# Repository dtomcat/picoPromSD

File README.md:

# picoPromSD
EEPROM reader/writer and OG Xbox Seagate Password retrieval for the Original Xbox that also decodes the EEPROM data

What will it do?

1. Backup the Xbox's EEPROM and save it to microSD card.
2. Can write an EEPROM backup saved to µSD card to the Xbox's EEPROM.  (has some checks to help prevent writing a bad backup to the EEPROM)
3. Decrypt the EEPROM and save the important information in plain text to the µSD card.
4. Can calculate the HDD password while backing up the EEPROM (for OEM Seagate and WD drives)
		- Requires preparing an additional file.  Video of process: [Video of Process](https://youtu.be/JSXaQWXcwFo?si=bOLGbLG80aQxxA59)
5. For OEM Seagate drives (ALL), It can grab the HDD password directly from the drive itself.  No need for EEPROM or XBOX.  [Video of Process](https://youtu.be/1lWm_fr0Neo?si=kcM-wwt6UB56qRjm)
6. For OEM Seagate drives (ALL), It can unlock the HDD directly from the drive itself.  No need for EEPROM or XBOX.  [Video of Slim](https://www.youtube.com/shorts/Nwhjg9Vyvl8), [Video of RJ](https://www.youtube.com/shorts/swidWJ0N5yo)
7. More features may be added later.
<br><br><br>
This project is based on the work from Ryzee119's ArduinoProm:

>ArduinoProm. An Arduino based Original Xbox EEPROM reader and writer.
>It can be used to recover a HDD key etc. <br><br>
>ArduinoProm is inspired and adapted upon the awesome work by Grimdoomer on PiPROM, now achievable on a <$3 Arduino board.
>See https://github.com/grimdoomer/PiPROM for the Original Raspberry Pi version!
>  
>**Use at your own risk**
>

>The firmware has been written around the Arduino Pro Micro Leonardo (5V/16Mhz). However I would expect it to work on any Arduino with a built in USB >bootloader/Virtual Comport support, and obviously I2C support.
>1. Open `ArduinoProm.ino` in [Arduino IDE](https://www.arduino.cc/en/main/software)
>2. Connect your Arduino to your PC and setup the IDE. An example below <br> 
>3. Hit the program button then confirm it compiles and programs successfully.
>
>
>By Ryzee119

This project uses code by Ryzee119, dx4m (from this [project](https://github.com/dx4m/Xbox-EEPROM-Utility)), and may contain code from various snippets from different forums (sorry lost my notes on who to thank).

This project is a continuation of my work from [ArdPromSD project](https://github.com/dtomcat/ArdPromSD).
This project was moved to an RP2040 MCU for more memory space.  This allowed me add the features I wanted to from the previous project, but ran out of program space to do so.  New features include better logging, eeprom decryption, as well as being able to retrieve the password from OEM seagate drives without the need for the original eeprom, original xbox, or even a PC!

SPECIAL THANKS!!!!<br>
Ryzee for his project above!<br>
Skye for all the HDD commands and knowledge! Invaluable addition to PPSD!<br>
Beta Testers:  Cato, Harcroft, Siktah

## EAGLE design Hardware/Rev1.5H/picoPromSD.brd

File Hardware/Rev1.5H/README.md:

## Initial release of picoPromSD
Initial release that contains everything needed to either make or have one assembled
This revision is an edit from the first release.  All edits were done by Harcroft who put a lot of time in effort into find same quality alternate parts at lower costs so picoPromSD could be build at a lower cost without sacrificing quality or functionality! <br><br>

<br>
<br>

In the main Rev1.5H directory are all the files to edit the board as you want including library of all components.

### Gerbers
- Contains all files necessary to have the PCBs made at your preferred PCB house.<br><br>

### Assembly
- Contains all files necessary to have the PCBs made and assemble at your preferred PCB house. (was made for JLCPCB, but may work with others)
    - [PicoPromSD_v1.5H_JLC_PCBA_BOM.xlsx](Assembly/PicoPromSD_v1.5H_JLC_PCBA_BOM.xlsx) and [PicoPromSD_v1.5H_top_JLC_CPL.csv](Assembly/PicoPromSD_v1.5H_top_JLC_CPL.csv) are the files JLCPCB will ask for when selecting assembly.
    - [PicoPromSD_v1.5H_LCSC_THT_BOM.xlsx](Assembly/PicoPromSD_v1.5H_LCSC_THT_BOM.xlsx) is the parts you'll need (from LCSC) that are not a part of the assembly and will need to be hand soldered on.  These are through hole components and were purposely omitted from the assembly to save costs since through hole adds a considerable amount to assembly costs.
    - [PicoPromSD_v1.5H_Digikey_BOM.xlsx] contains a full BOM to allow you to order all the parts and hand assemble the entire board. (or would just like to use parts from Digikey instead of LCSC).

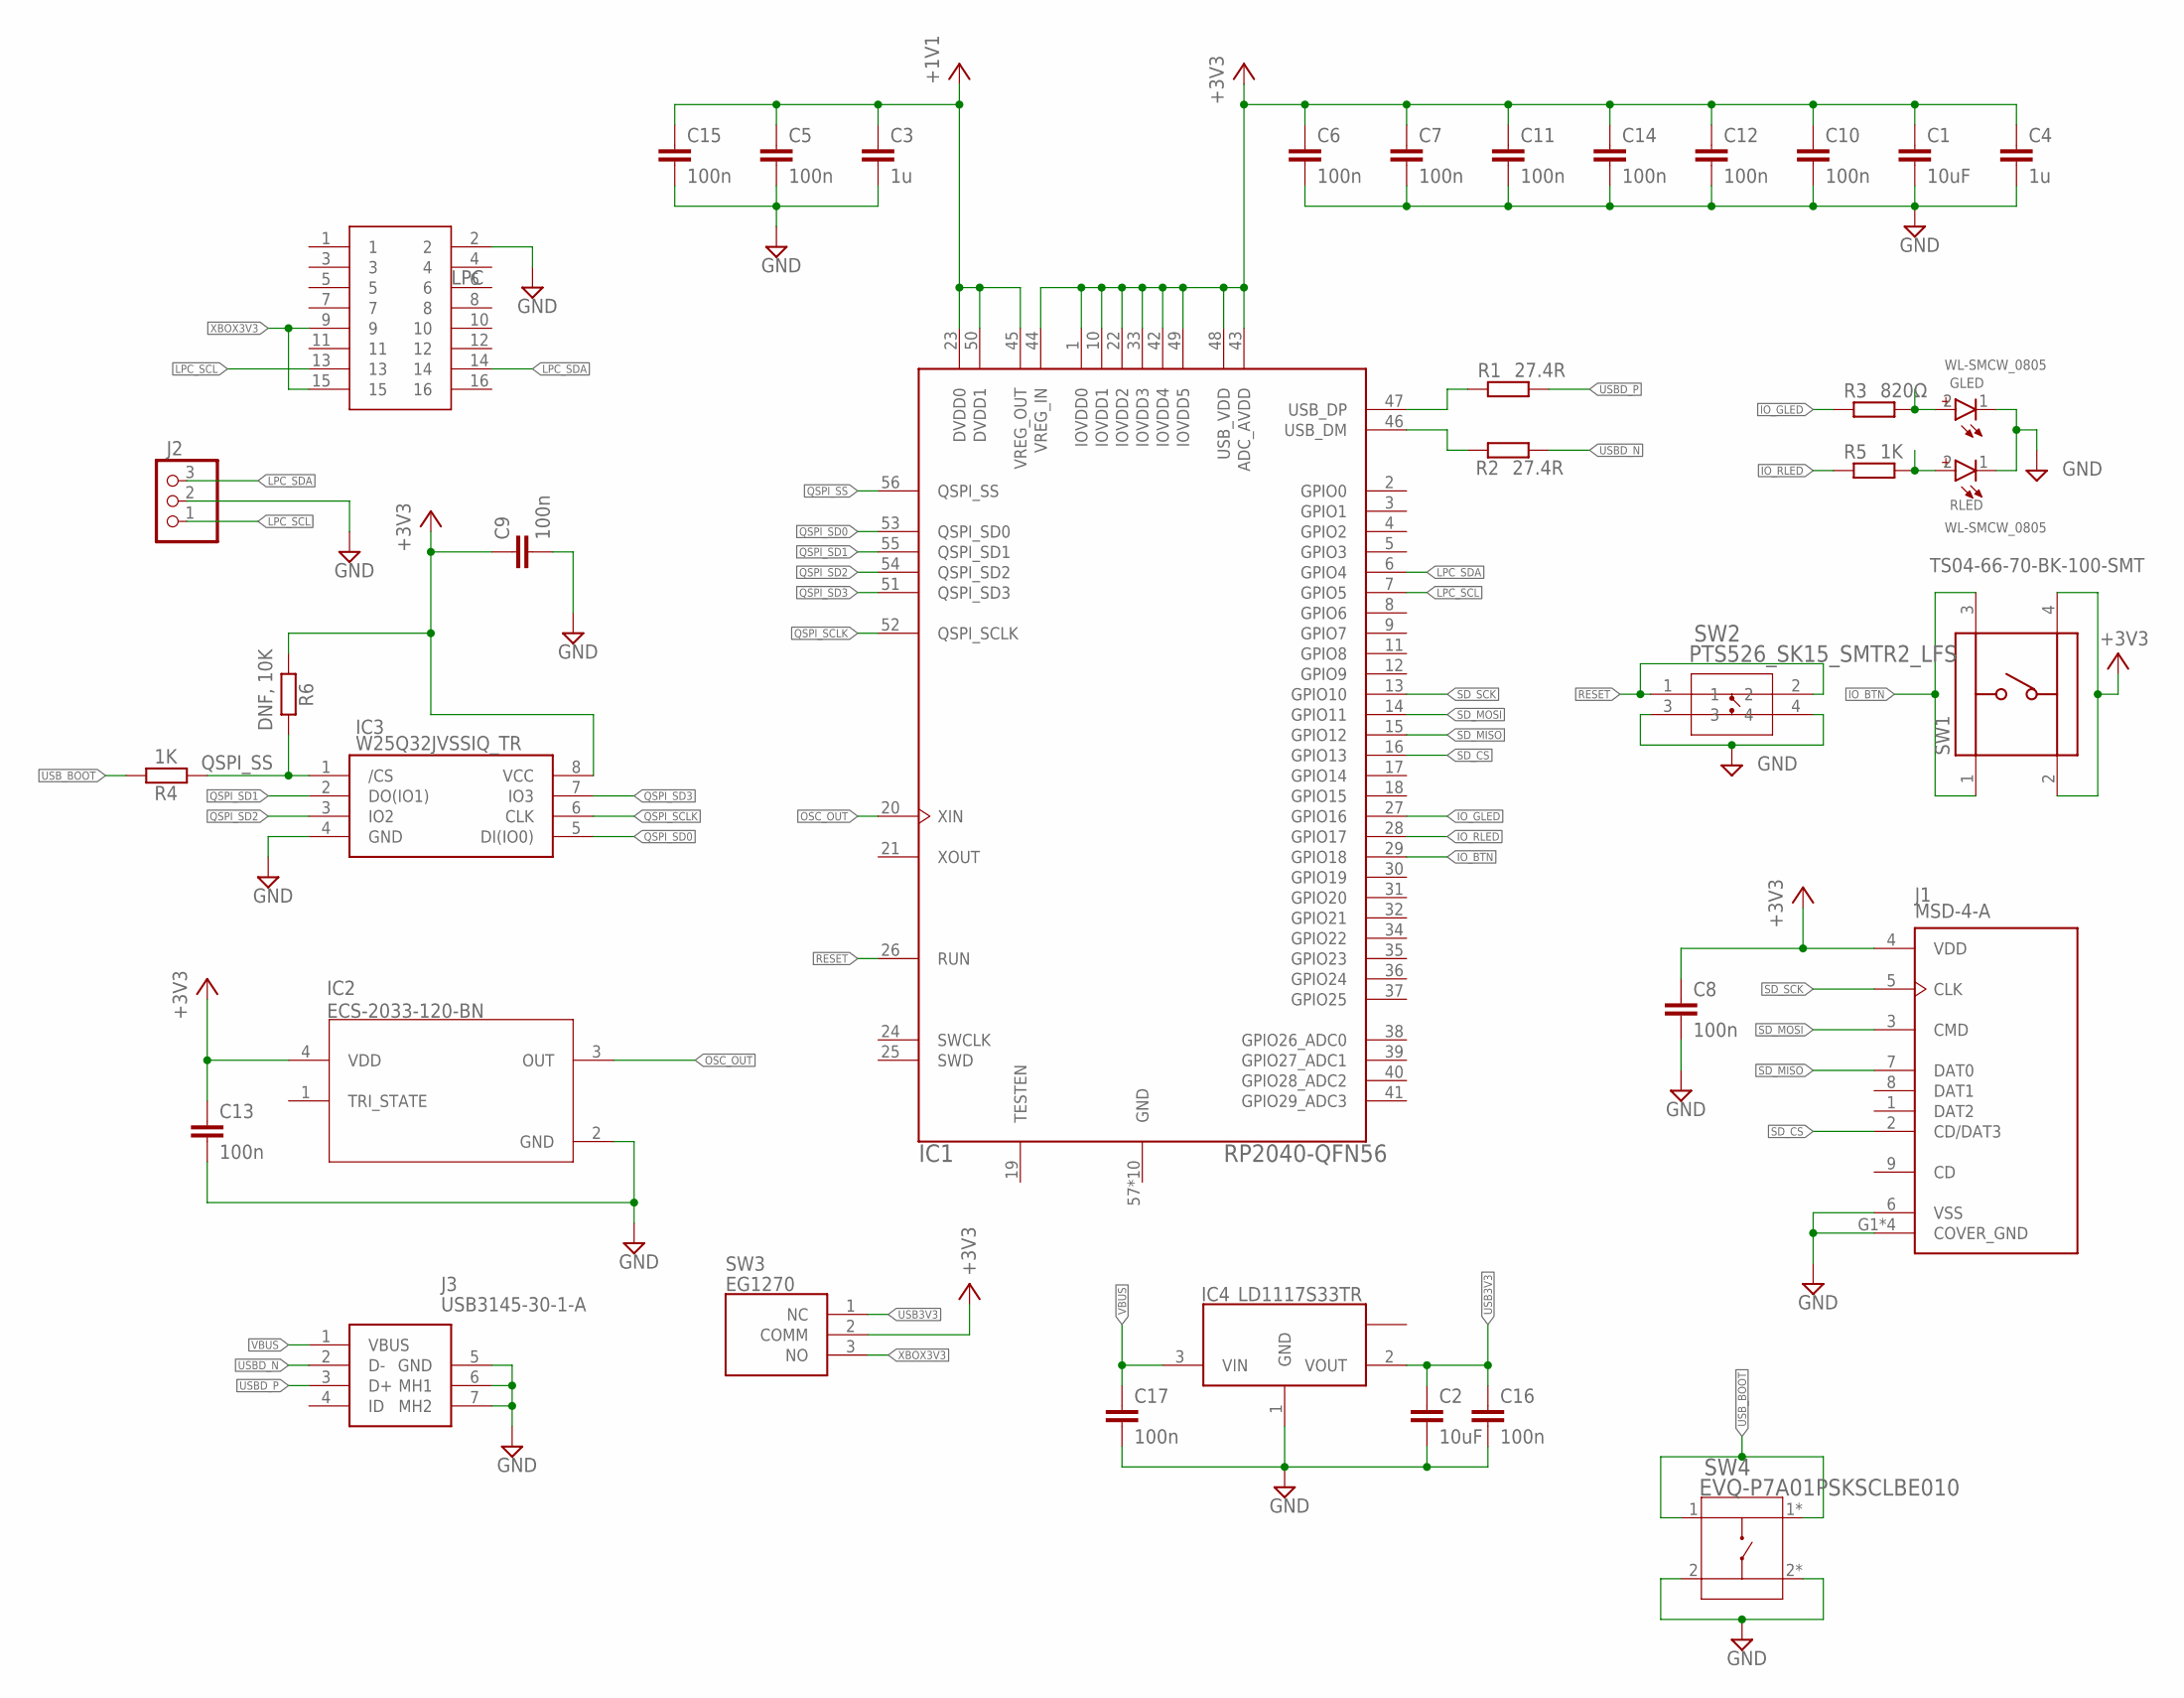
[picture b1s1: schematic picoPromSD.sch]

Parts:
C1, C2: 10uF; C0603
C3, C4: 1u; C0402
C5, C6, C7, C8, C9, C10, C11, C12, C13, C14, C15, C16, C17: 100n; C0402
GLED: WL-SMCW_0805
IC1: RP2040-QFN56; RP2040-QFN-56
IC2: ECS-2033-120-BN; OSC_ECS-2033-120-BN
IC3: W25Q32JVSSIQ_TR; SOIC127P790X216-8N
IC4: LD1117S33TR; SOT223
J1: MSD-4-A; CUI_MSD-4-A
J2: PINHEAD_2.54MM_1X3
J3: USB3145-30-1-A; USB3145301A
LPC: PINHEAD_2.54MM_2X8
R1, R2: 27.4R; R0402
R3: 820Ω; R0402
R4, R5: 1K; R0402
R6: DNF, 10K; R0402
RLED: WL-SMCW_0805
SW1: TS04-66-70-BK-100-SMT; SW_TS04-66-70-BK-100-SMT
SW2: PTS526_SK15_SMTR2_LFS; SMT_FS
SW3: EG1270
SW4: EVQ-P7A01PSKSCLBE010; SKSCLBE010

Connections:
+3V3: C1.1, C4.1, C6.1, C7.1, C8.1, C9.1, C10.1, C11.1, C12.1, C13.1, C14.1, IC1.1 (IOVDD0), IC1.10 (IOVDD1), IC1.22 (IOVDD2), IC1.33 (IOVDD3), IC1.42 (IOVDD4), IC1.43 (ADC_AVDD), IC1.44 (VREG_IN), IC1.48 (USB_VDD), IC1.49 (IOVDD5), IC2.4 (VDD), IC3.8 (VCC), J1.4 (VDD), R6.2, SW1.2, SW1.4, SW3.2 (COMM)
GND: C1.2, C2.2, C3.2, C4.2, C5.2, C6.2, C7.2, C8.2, C9.2, C10.2, C11.2, C12.2, C13.2, C14.2, C15.2, C16.2, C17.2, GLED.1 (-), IC1.57 (GND), IC1.58 (GND), IC1.59 (GND), IC1.60 (GND), IC1.61 (GND), IC1.62 (GND), IC1.63 (GND), IC1.64 (GND), IC1.65 (GND), IC1.66 (GND), IC2.2 (GND), IC3.4 (GND), IC4.1 (GND), J1.6 (VSS), J1.G1 (COVER_GND), J1.G2 (COVER_GND), J1.G3 (COVER_GND), J1.G4 (COVER_GND), J2.2, J3.5 (GND), J3.6 (MH1), J3.7 (MH2), LPC.2, RLED.1 (-), SW2.3, SW2.4, SW4.2, SW4.2* (!)
IO_BTN: IC1.29 (GPIO18), SW1.1, SW1.3
IO_GLED: IC1.27 (GPIO16), R3.1
IO_GLED2: GLED.2 (+), R3.2
IO_RLED: IC1.28 (GPIO17), R5.1
IO_RLED2: R5.2, RLED.2 (+)
LPC_SCL: IC1.7 (GPIO5), J2.1, LPC.13
LPC_SDA: IC1.6 (GPIO4), J2.3, LPC.14
OSC_OUT: IC1.20 (XIN), IC2.3 (OUT)
PUSBD_N: IC1.46 (USB_DM), R2.1
PUSBD_P: IC1.47 (USB_DP), R1.1
QSPI_SCLK: IC1.52 (QSPI_SCLK), IC3.6 (CLK)
QSPI_SD0: IC1.53 (QSPI_SD0), IC3.5 (DI(IO0))
QSPI_SD1: IC1.55 (QSPI_SD1), IC3.2 (DO(IO1))
QSPI_SD2: IC1.54 (QSPI_SD2), IC3.3 (IO2)
QSPI_SD3: IC1.51 (QSPI_SD3), IC3.7 (IO3)
QSPI_SS: IC1.56 (QSPI_SS), IC3.1 (/CS), R4.2, R6.1
RESET: IC1.26 (RUN), SW2.1, SW2.2
SD_CS: IC1.16 (GPIO13), J1.2 (CD/DAT3)
SD_MISO: IC1.15 (GPIO12), J1.7 (DAT0)
SD_MOSI: IC1.14 (GPIO11), J1.3 (CMD)
SD_SCK: IC1.13 (GPIO10), J1.5 (CLK)
USB3V3: C2.1, C16.1, IC4.2 (VOUT), SW3.1 (NC)
USBD_N: J3.2 (D-), R2.2
USBD_P: J3.3 (D+), R1.2
USB_BOOT: R4.1, SW4.1, SW4.1* (!_2)
VBUS: C17.1, IC4.3 (VIN), J3.1 (VBUS)
VCC: C3.1, C5.1, C15.1, IC1.23 (DVDD0), IC1.45 (VREG_OUT), IC1.50 (DVDD1)
XBOX3V3: LPC.9, LPC.15, SW3.3 (NO)

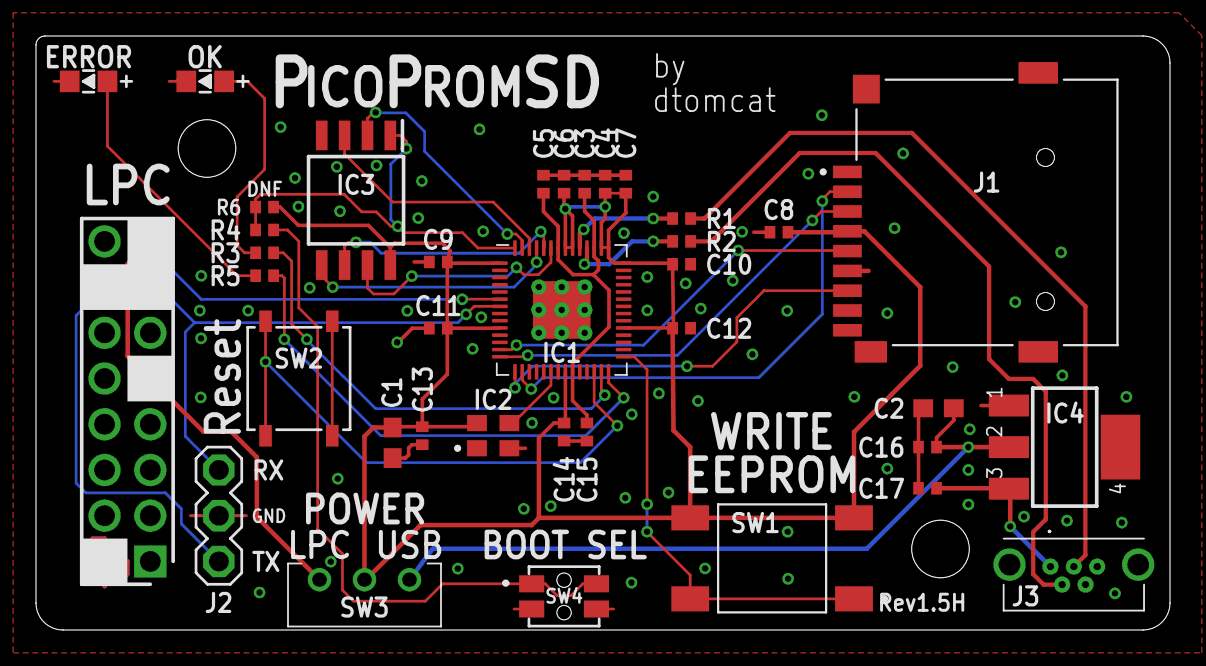
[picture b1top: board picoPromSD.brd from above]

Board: 2 copper layers, 63.0 x 33.0 mm, 38 parts (1 on the bottom side), 30 nets.

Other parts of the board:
U$1: POGO_SILK

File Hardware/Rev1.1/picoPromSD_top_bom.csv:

Comment,Designator,Footprint,LCSC Part #
1K,GLED R5 R6 RLED R4,R0402,
1u,C1 C4,C0402,
10uF,C18,C0603,
27R,R1 R2,R0402,
100n,C2 C3 C5 C6 C7 C8 C9 C10 C11 C12 C13 C14 C15 C16 C17,C0402,
DNF  10K,R3,R0402,
EVQ-P7A01P,S4,EVQP7J01P,
LD1117S33TR,IC4,SOT223,
MEM2075-00-140-01-A,J1,MEM20750014001A,
RP2040-QFN56,IC1,RP2040-QFN-56,
SIT2001B,IC2,SOT95P280X130-5N,
TL6330AF200Q,S2,TL6330AF200Q,
TS04-66-70-BK-100-SMT,S1,SW_TS04-66-70-BK-100-SMT,
W25Q32JVSSIQ_TR,IC3,SOIC127P790X216-8N,

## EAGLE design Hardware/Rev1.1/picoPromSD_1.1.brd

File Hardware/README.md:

1.1 is the initial released version.  Those who backed the initial project and funded it have a limited edition 1.0a version (Thank you!).  This will not be released and is solely for the limited backers.  1.1 just has minor trace redesigns and the "Advanced users" port has been removed.  Version 1.5H has already been designed and as soon as it's tested, It will be uploaded.  I do not recommend building rev 1.1 as 1.5H has major changes to the board to allow for lower cost builds.  Functionally, they will be the same.  Enjoy!<br><br>

# Rev 1.1 - 12DEC2024
Initial Release (No Gerbers or Assembly info for this release.  1.5H and above will have them.)

# Rev 1.5H - 02JAN2025
Happy New Year!  1.5H released (rework done by Harcroft - Thank you!  Allows for lower cost build with same quality and funcionality) This is a full release with everything you need to build one, or have one assembled.

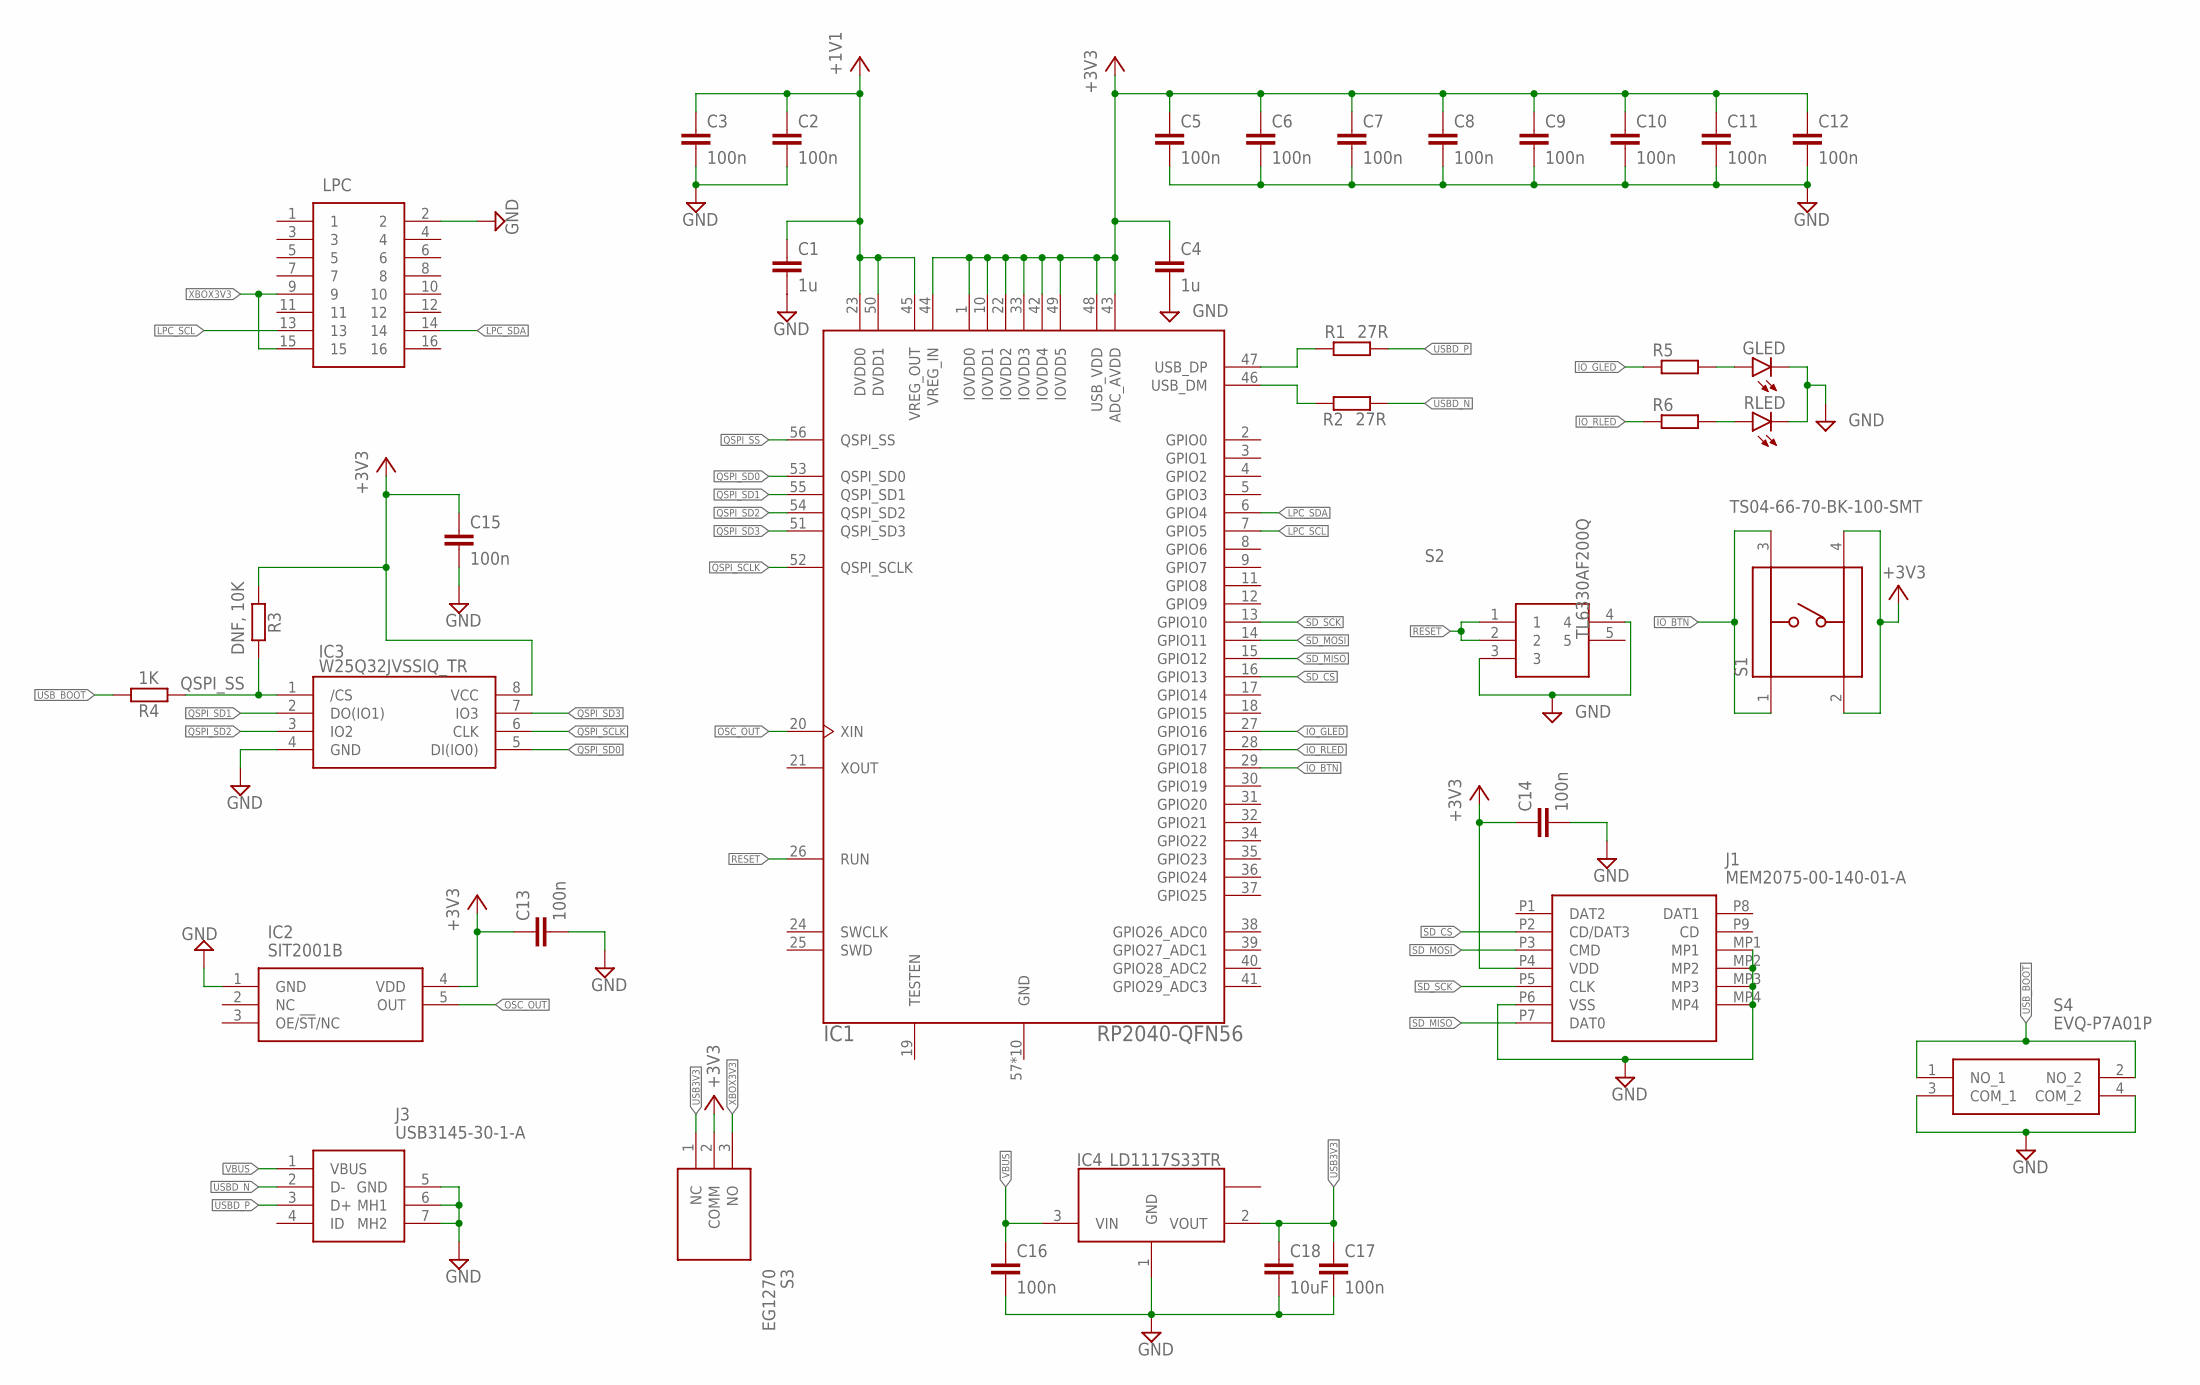
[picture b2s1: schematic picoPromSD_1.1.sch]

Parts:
C1, C4: 1u; C0402
C2, C3, C5, C6, C7, C8, C9, C10, C11, C12, C13, C14, C15, C16, C17: 100n; C0402
C18: 10uF; C0603
GLED: LED_LEDGREEN; GHI-BASICCOMPONENTS_0805-LED
IC1: RP2040-QFN56; RP2040-QFN-56
IC2: SIT2001B; SOT95P280X130-5N
IC3: W25Q32JVSSIQ_TR; SOIC127P790X216-8N
IC4: LD1117S33TR; SOT223
J1: MEM2075-00-140-01-A; MEM20750014001A
J3: USB3145-30-1-A; USB3145301A
LPC: 61301621821; RHDR16W79P254X254_2X8_2082X508
R1, R2: 27R; R0402
R3: DNF, 10K; R0402
R4: 1K; R0402
R5, R6: R-EU_R0402; R0402
RLED: LED_LEDRED; CHIP-LED0805
S1: TS04-66-70-BK-100-SMT; SW_TS04-66-70-BK-100-SMT
S2: TL6330AF200Q
S3: EG1270
S4: EVQ-P7A01P; EVQP7J01P

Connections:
+3V3: C4.1, C5.1, C6.1, C7.1, C8.1, C9.1, C10.1, C11.1, C12.1, C13.1, C14.1, C15.1, IC1.1 (IOVDD0), IC1.10 (IOVDD1), IC1.22 (IOVDD2), IC1.33 (IOVDD3), IC1.42 (IOVDD4), IC1.43 (ADC_AVDD), IC1.44 (VREG_IN), IC1.48 (USB_VDD), IC1.49 (IOVDD5), IC2.4 (VDD), IC3.8 (VCC), J1.P4 (VDD), R3.2, S1.2, S1.4, S3.2 (COMM)
GND: C1.2, C2.2, C3.2, C4.2, C5.2, C6.2, C7.2, C8.2, C9.2, C10.2, C11.2, C12.2, C13.2, C14.2, C15.2, C16.2, C17.2, C18.2, GLED.K (C), IC1.57 (GND), IC1.58 (GND), IC1.59 (GND), IC1.60 (GND), IC1.61 (GND), IC1.62 (GND), IC1.63 (GND), IC1.64 (GND), IC1.65 (GND), IC1.66 (GND), IC2.1 (GND), IC3.4 (GND), IC4.1 (GND), J1.MP1, J1.MP2, J1.MP3, J1.MP4, J1.P6 (VSS), J3.5 (GND), J3.6 (MH1), J3.7 (MH2), LPC.2, RLED.C, S2.3, S2.4, S4.3 (COM_1), S4.4 (COM_2)
IO_BTN: IC1.29 (GPIO18), S1.1, S1.3
IO_GLED: IC1.27 (GPIO16), R5.1
IO_RLED: IC1.28 (GPIO17), R6.1
LPC_SCL: IC1.7 (GPIO5), LPC.13
LPC_SDA: IC1.6 (GPIO4), LPC.14
unnamed: GLED.A, R5.2
unnamed: R6.2, RLED.A
OSC_OUT: IC1.20 (XIN), IC2.5 (OUT)
PUSBD_N: IC1.46 (USB_DM), R2.1
PUSBD_P: IC1.47 (USB_DP), R1.1
QSPI_SCLK: IC1.52 (QSPI_SCLK), IC3.6 (CLK)
QSPI_SD0: IC1.53 (QSPI_SD0), IC3.5 (DI(IO0))
QSPI_SD1: IC1.55 (QSPI_SD1), IC3.2 (DO(IO1))
QSPI_SD2: IC1.54 (QSPI_SD2), IC3.3 (IO2)
QSPI_SD3: IC1.51 (QSPI_SD3), IC3.7 (IO3)
QSPI_SS: IC1.56 (QSPI_SS), IC3.1 (/CS), R3.1, R4.2
RESET: IC1.26 (RUN), S2.1, S2.2
SD_CS: IC1.16 (GPIO13), J1.P2 (CD/DAT3)
SD_MISO: IC1.15 (GPIO12), J1.P7 (DAT0)
SD_MOSI: IC1.14 (GPIO11), J1.P3 (CMD)
SD_SCK: IC1.13 (GPIO10), J1.P5 (CLK)
USB3V3: C17.1, C18.1, IC4.2 (VOUT), S3.1 (NC)
USBD_N: J3.2 (D-), R2.2
USBD_P: J3.3 (D+), R1.2
USB_BOOT: R4.1, S4.1 (NO_1), S4.2 (NO_2)
VBUS: C16.1, IC4.3 (VIN), J3.1 (VBUS)
VCC: C1.1, C2.1, C3.1, IC1.23 (DVDD0), IC1.45 (VREG_OUT), IC1.50 (DVDD1)
XBOX3V3: LPC.9, LPC.15, S3.3 (NO)

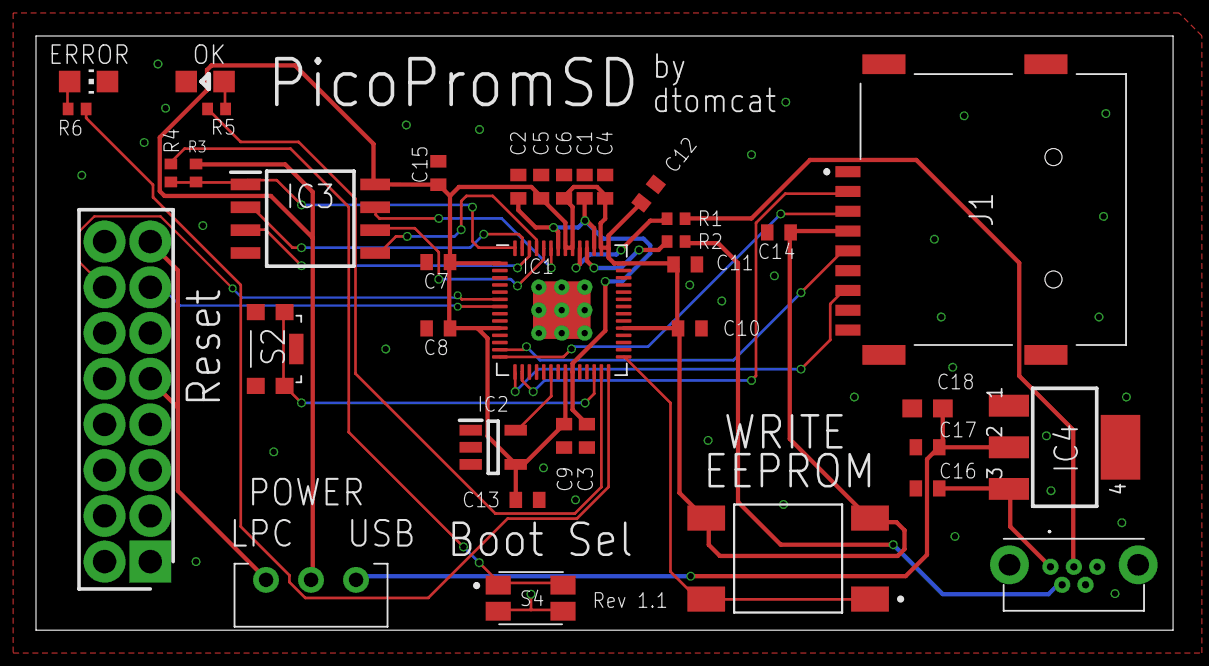
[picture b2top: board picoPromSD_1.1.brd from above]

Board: 2 copper layers, 63.2 x 33.0 mm, 37 parts (0 on the bottom side), 30 nets.

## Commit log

2023-11-01 Create changelog.md
    Adding Firmware
2023-11-01 Rename changelog.md to Readme.md
2023-11-01 Rename Readme.md to README.md
2023-11-28 Adds folder support
2024-07-08 Preparing to open source
2024-12-10 Initial Source Code upload
    Uploading source code for V2.3 (latest version as of upload). Initial release for Open Source.
2024-12-13 Initial Hardware upload
    Uploading rev 1.1 (do not recommend building this rev)... Wait for 1.5H (soon... in testing)
2025-01-02 1.5H upload
    Upload of Rev1.5H and all files necessary to make or have one assembled.
2025-01-30 List what the picoPromSD does
2025-01-30 Uploading 2.4 firmware
    Uploading v2.4 firmware and updating supporting documents.
2025-01-30 Fix directory naming
2025-01-30 Typo
2025-01-30 Fixed for directory naming change
2025-03-03 FW 3.0 upload and readme updates
    Uploading FW 3.0 and changed readme to include what new firmware does and added thank you section
2025-03-04 Update userManual.pdf
    Add HDD unlocking to User Manual

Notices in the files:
parts and their libraries:
COPYRIGHT: Copyright (C) 2024 Ultra Librarian. All rights reserved.
